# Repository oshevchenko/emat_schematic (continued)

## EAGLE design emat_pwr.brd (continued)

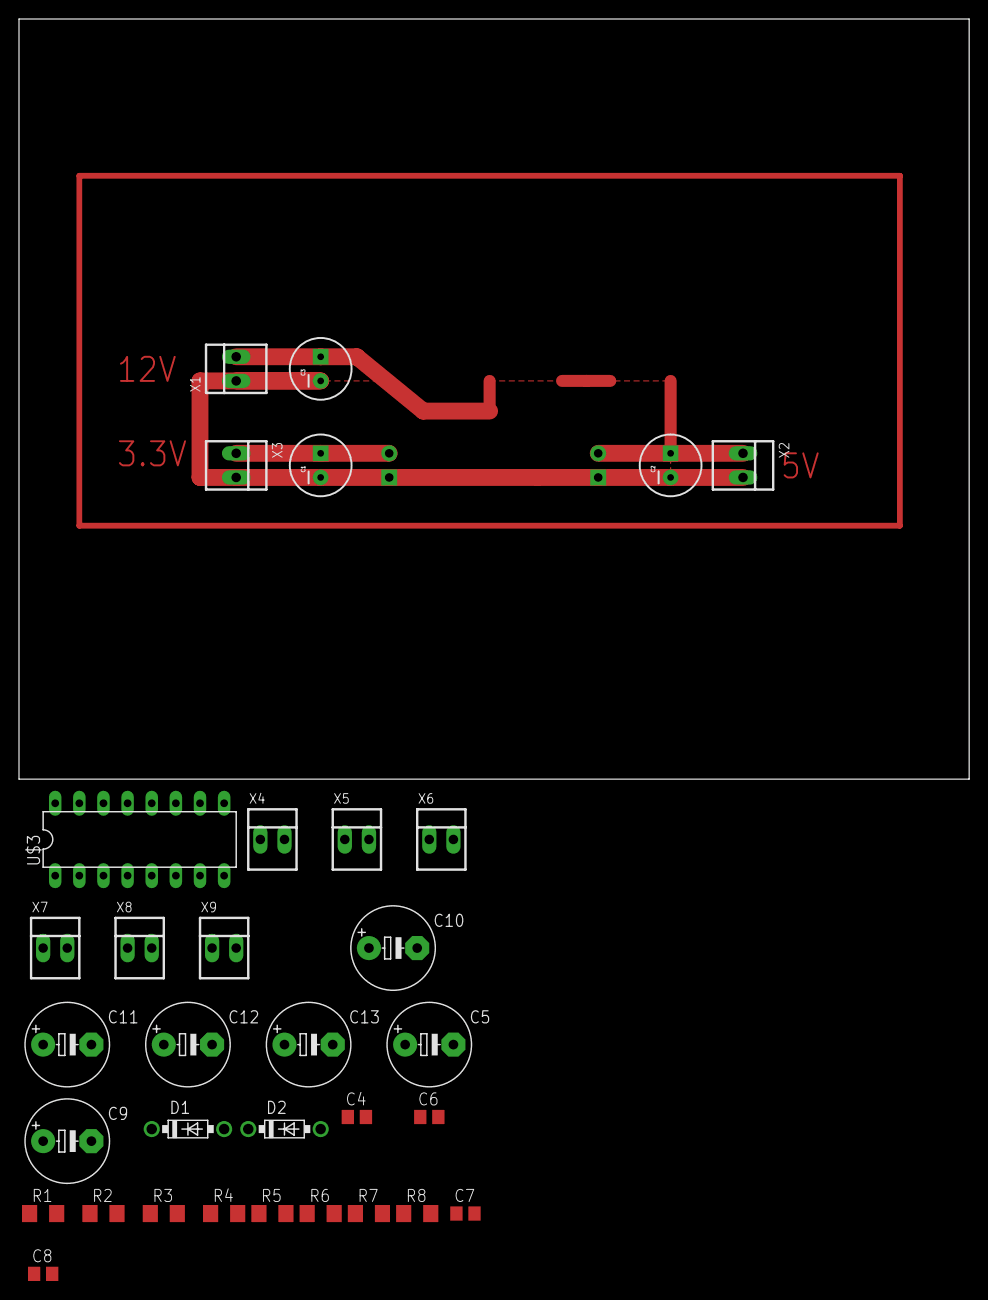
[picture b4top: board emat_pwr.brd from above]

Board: 2 copper layers, 100.0 x 80.0 mm, 34 parts (1 on the bottom side), 20 nets.

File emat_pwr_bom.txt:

Partlist exported from D:/workspace/EMAT/POC/Schematic/Emat/emat_pwr.sch at 5/11/2016 3:17 PM

Qty Value       Device             Package               Parts                              Description                          MF    MPN        OC_FARNELL OC_NEWARK PROD_ID  

1   100         R-US_R1206         R1206                 R6                                 RESISTOR, American symbol                                                           
3   4.7K        R-US_R1206         R1206                 R1, R2, R3                         RESISTOR, American symbol                                                           
3   12K         R-US_R1206         R1206                 R4, R7, R8                         RESISTOR, American symbol                                                           
1   20K         R-US_R1206         R1206                 R5                                 RESISTOR, American symbol                                                           

2   1nF         C-EUC0805          C0805                 C7, C8                             CAPACITOR, European symbol                                                          
2   100nF       C-EUC0805          C0805                 C4, C6                             CAPACITOR, European symbol                                                          

1   22uF 25V    CPOL-USE5-8.5      E5-8,5                C9                                 POLARIZED CAPACITOR, American symbol                                                
3   100uF 25V   100UF-25V-20%(PTH) CPOL-RADIAL-100UF-25V C1, C2, C3                         CAP-08439                                                                  CAP-08439
5   220uF 25V   CPOL-USE5-8.5      E5-8,5                C5, C10, C11, C12, C13             POLARIZED CAPACITOR, American symbol                                                

1   SG3525N     SG3525N            DIP16                 U$3                                                                                                                    
2   UF4004      DIODE-DO41-7.6     DO41-7.6              D1, D2                             DIODE

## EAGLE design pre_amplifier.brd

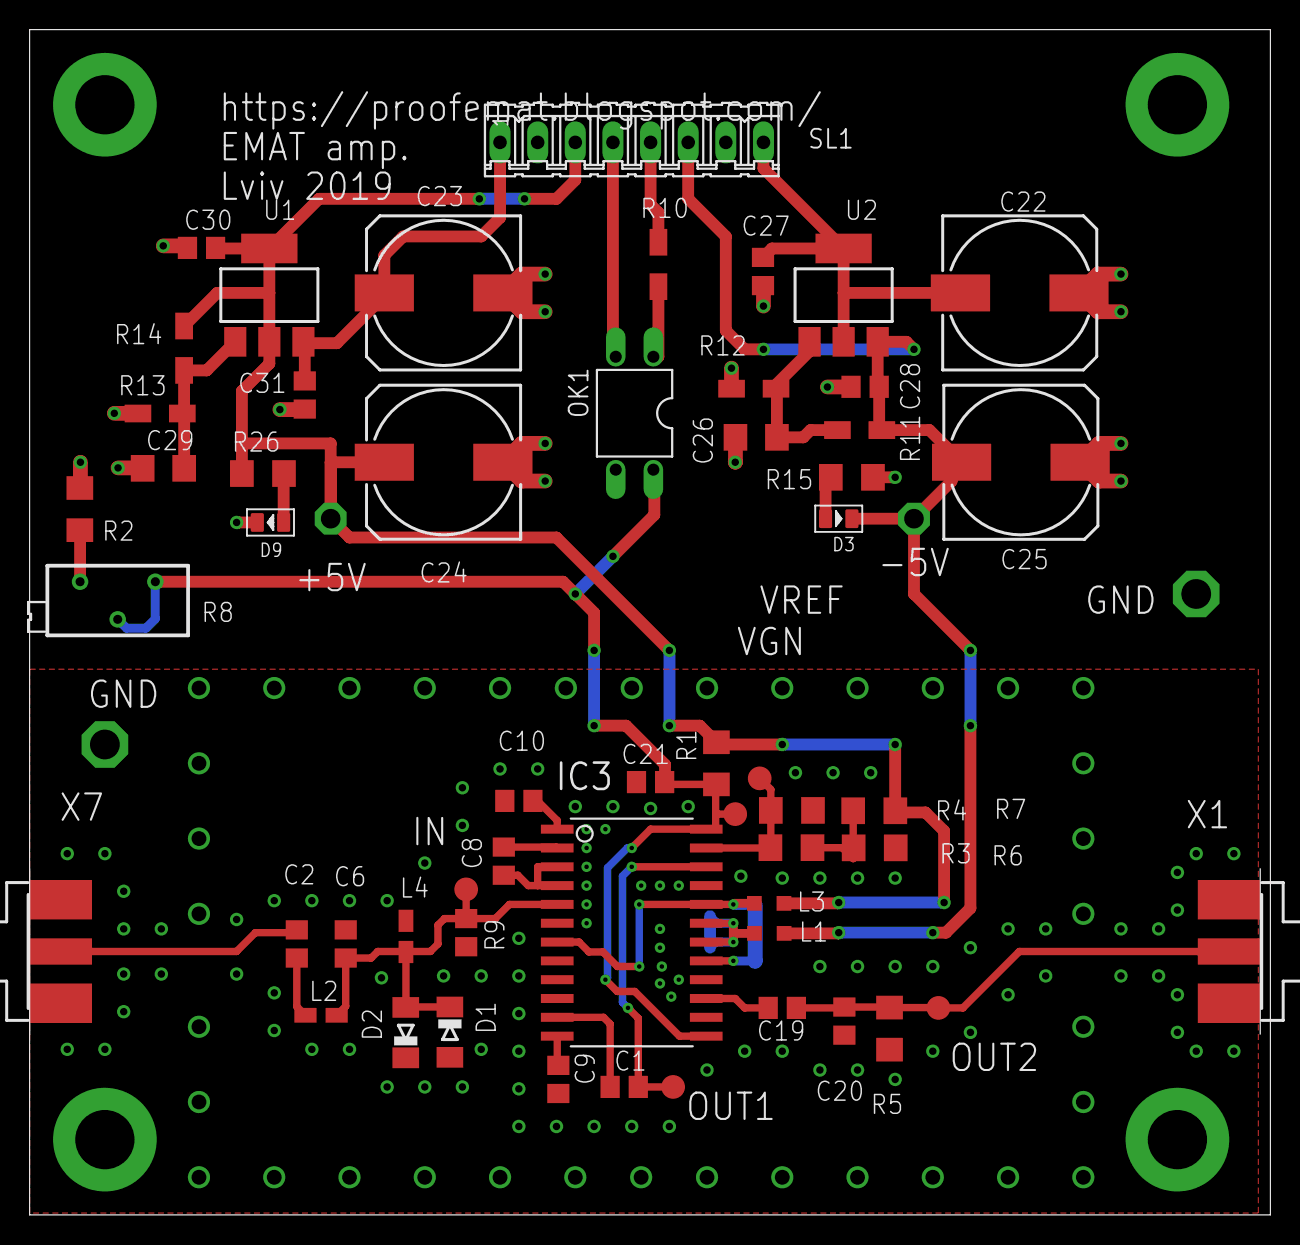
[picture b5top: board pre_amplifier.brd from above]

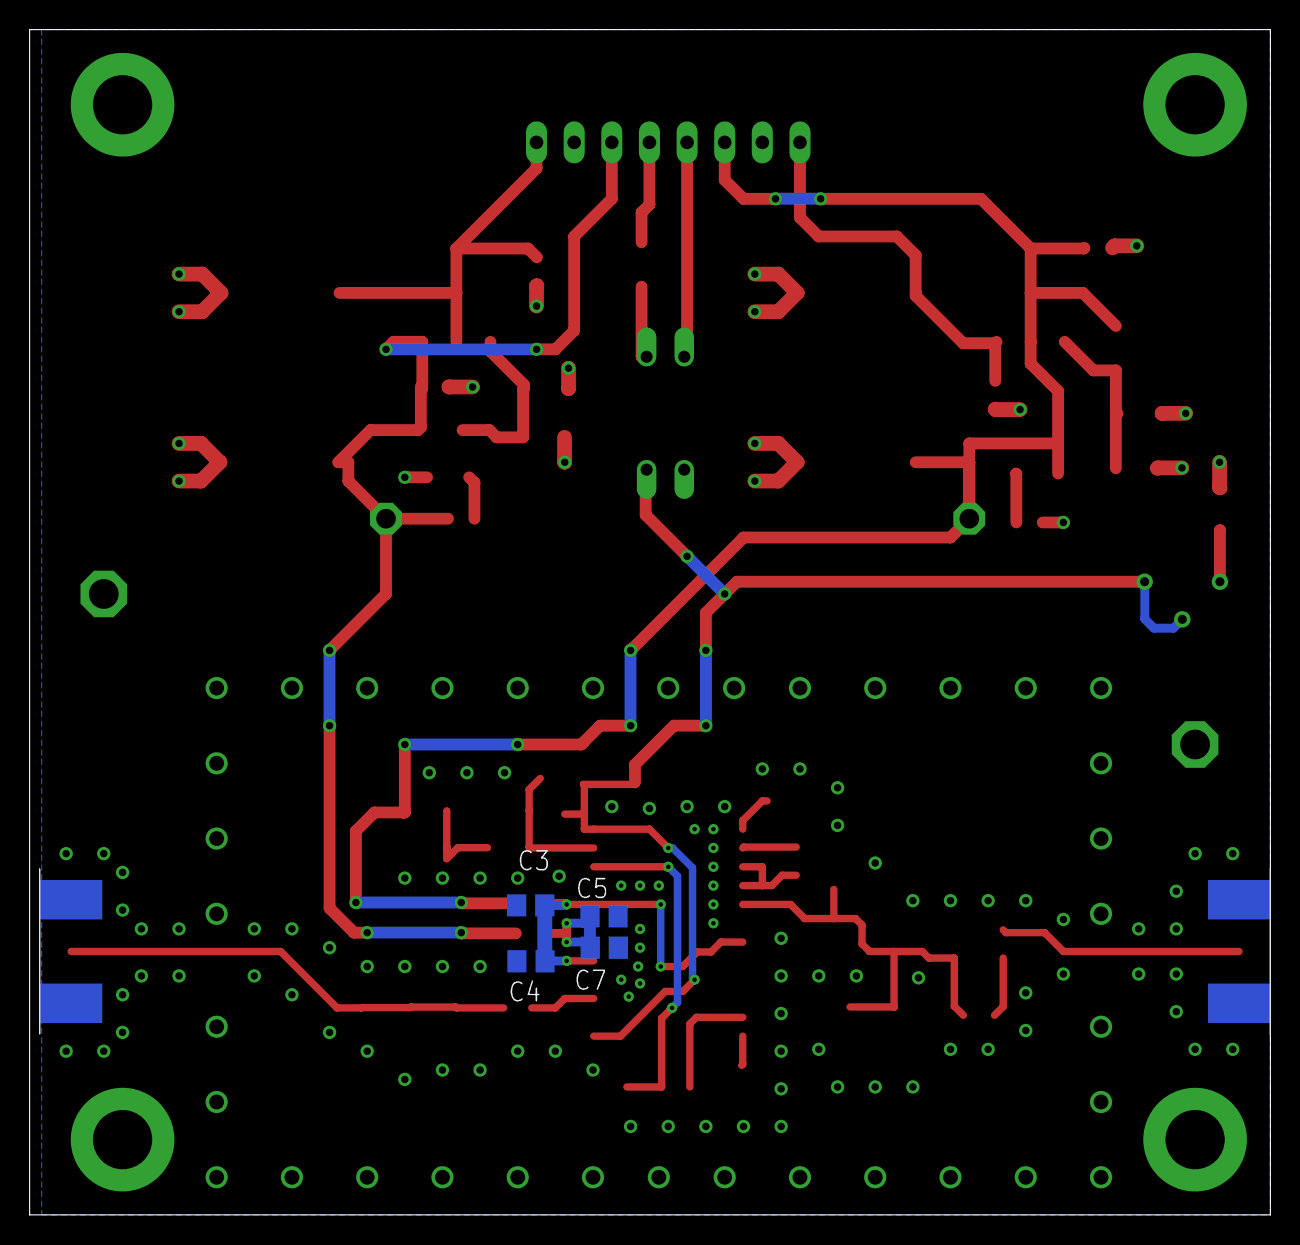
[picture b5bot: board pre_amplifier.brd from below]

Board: 2 copper layers, 83.7 x 80.0 mm, 63 parts (4 on the bottom side), 29 nets.

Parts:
C1, C3, C4, C5, C7, C8, C9, C10, C19, C27, C31: 100nF; C0805
C2: 2.4nF; C0805
C6: 12nF; C0805
C20: 5pF; C0805
C21: 100pF; C0805
C22, C23: 220uF 16V; 153CLV-1010
C24, C25: 470uF 6.3V; 153CLV-1010
C26, C29: 10uF; C1206
C28, C30: 1uF; C0805
D1, D2: 1N4148; MINIMELF
D3: -5V; LED-0805
D9: +5V; LED-0805
IC3: SO24L
L1, L3: BLM21PG221SN1D; L2012C
L2: 10uH; L0805W
L4: 2.2uH; L0805W
OK1: PC817; DIL04
R1: 20K; R1206
R2, R15, R26: 1K; R1206
R3, R7: 5.1K; R1206
R4: 47K; R1206
R5: 510; R1206
R6: 10K; R1206
R8: 20K; RTRIMT93XB
R9: 51; R0805
R10: 510; R1206W
R11, R14: 240; R1206W
R12, R13: 720; R1206W
SL1: 08P
TP1, TP2: TPSQPAD1-13; P1-13
TP3, TP4, TP5, TP6, TP7: TPSQTP16R; TP16R
TP8, TP9: TPSQPAD1-20; P1-20
U1: LM317DCY; SOT223
U2: LM337IMP; SOT223
X1, X7: SMA-142-0711-821/826; J502-ND-142-0711-821/826

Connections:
+5V: C24.+, C30.2, L3.1, R1.2, R7.2, R14.2, R26.2, SL1.3, TP1.TP, U1.2, U1.4
+9V: C23.+, C31.2, SL1.1, U1.3
-5V: C25.-, C28.1, D3.-, L1.1, R11.1, SL1.6, TP2.TP, U2.3
-9V: C22.-, C27.1, SL1.8, U2.2, U2.4
GND: C3.2, C4.2, C5.1, C6.1, C7.1, C9.2, C10.1, C20.2, C21.2, C22.+, C23.-, C24.-, C25.+, C26.2, C27.2, C28.2, C29.1, C30.1, C31.1, D1.A, D2.C, D9.-, IC3.6, IC3.16, IC3.21, L4.2, OK1.3, R2.1, R4.1, R5.1, R6.1, R9.1, R12.2, R13.1, R15.2, SL1.2, SL1.7, TP8.TP, TP9.TP, X1.G@1, X1.G@2, X1.G@3, X1.G@4, X7.G@1, X7.G@2, X7.G@3, X7.G@4
unnamed: C21.1, IC3.13, IC3.24, OK1.4, R1.1, R8.1, R8.2, TP3.TP
unnamed: C9.1, IC3.12
unnamed: C6.2, D1.C, D2.A, IC3.5, L2.2, L4.1, R9.2, TP7.TP
unnamed: C19.1, C20.1, R5.2, TP6.TP, X1.1
unnamed: IC3.23, R3.1, R4.2, TP4.TP
unnamed: C1.2, IC3.22, TP5.TP
unnamed: C8.2, IC3.3, IC3.4
unnamed: C1.1, IC3.11
unnamed: C8.1, IC3.2
unnamed: C2.1, X7.1
unnamed: R2.2, R8.3
unnamed: R3.2, R6.2, R7.1
unnamed: C26.1, R11.2, R12.1, U2.1
unnamed: C10.2, IC3.1
unnamed: C2.2, L2.1
unnamed: C29.2, R13.2, R14.1, U1.1
unnamed: OK1.1, R10.2
unnamed: C19.2, IC3.15
unnamed: R10.1, SL1.5
unnamed: OK1.2, SL1.4
unnamed: D3.+, R15.1
unnamed: D9.+, R26.1
V+: C3.1, C4.1, IC3.7, IC3.17, IC3.20, L3.2
V-: C5.2, C7.2, IC3.18, IC3.19, L1.2

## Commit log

2019-05-06 Add current schematics.
